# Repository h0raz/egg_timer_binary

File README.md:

egg_timer_binary
===================

This is/will be a egg timer with a battery powered binary display

It shows either the minutes in 6 bits and the seconds or if time is greater than one hour the hour and the minutes and the seconds ticking

If the timer reaches zero it will beep until the rotary encoder is pressed

While the timer is not active you can change the timer by turning the encoder. Start/Pause, Reset is a Push on the encoder

If the seconds are not zero(eg you paused it) and you change the time the seconds will be set to 0

I set the OSCCAL so the drift is minimal and I don't need any crystal

As you can asume this project is still in development

The firmware is functional and finished for now but the layout needs some tweaking and I'm currently searching for a case which has the right size

> **Todo/Bugs:**
> 
> - Power down mode after a timeout
> - generalize Pin/Port settings
> - translate comments etc.
> - sound is a bit aweful
> - PCB desing
> - find case

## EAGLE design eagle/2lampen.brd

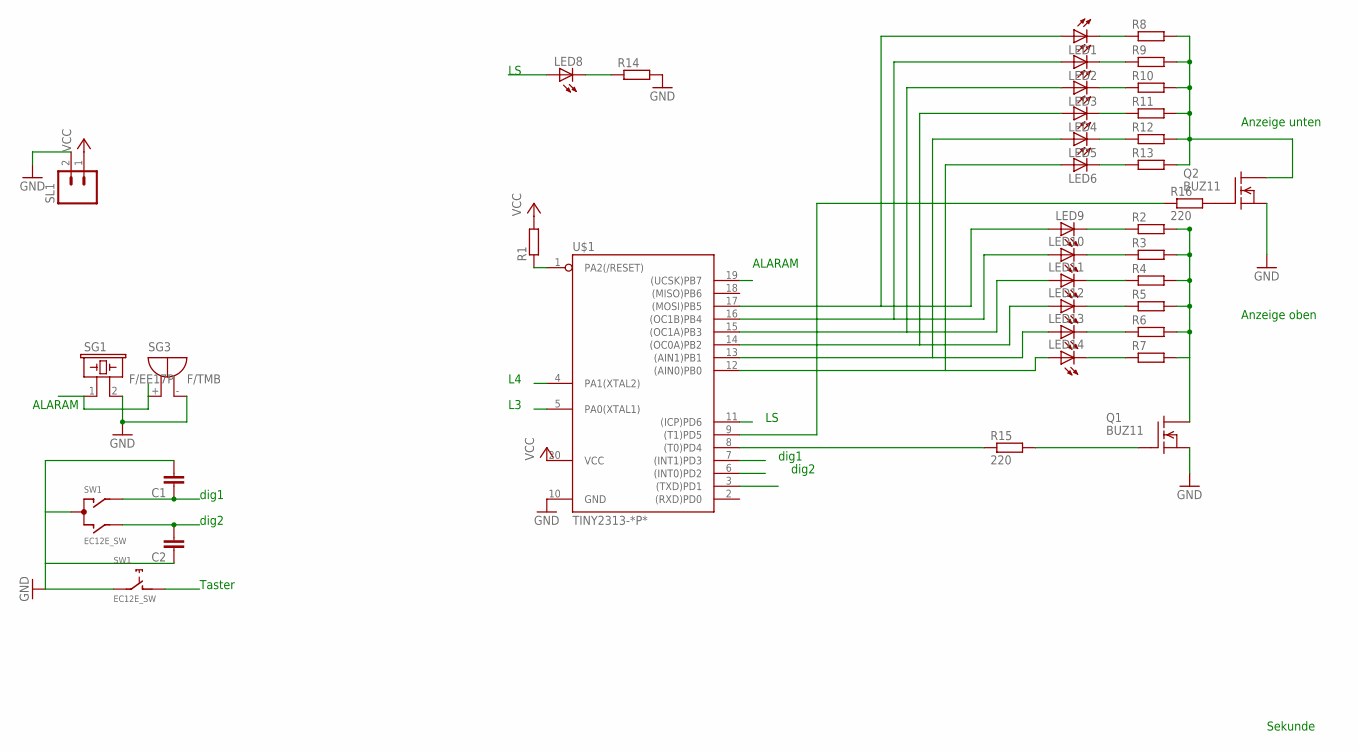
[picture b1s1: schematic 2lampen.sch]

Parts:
C1, C2: C-EU025-025X050; C025-025X050
LED1, LED2, LED3, LED4, LED5, LED6, LED9, LED10, LED11, LED12, LED13, LED14: LED5MM
LED8: LED3MM
Q1, Q2: BUZ11; TO220
R1, R13: R-EU_0204/7; 0204/7
R2, R3, R4, R5, R6, R7, R8, R9, R10, R11, R12, R14: R-EU_0204/2V; 0204V
R15, R16: 220; 0204V
SG1: F/EE17P
SG3: F/TMB
SL1: M02; 02P
SW1: EC12E_SW; ALPS_EC12E_SW
U$1: TINY2313-*P*; DIL20

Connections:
ALARM: SG1.1, SG3.+, U$1.19 ((UCSK)PB7)
DIG1: C1.1, SW1.A, U$1.7 ((INT1)PD3)
DIG2: C2.2, SW1.B, U$1.6 ((INT0)PD2)
GND: C1.2, C2.1, Q1.3 (S), Q2.3 (S), R14.2, SG1.2, SG3.-, SL1.2, SW1.C, SW1.E (2), U$1.10 (GND)
L1: LED1.A, LED9.A, U$1.17 ((MOSI)PB5)
L2: LED2.A, LED10.A, U$1.16 ((OC1B)PB4)
L3: LED3.A, LED11.A, U$1.5 (PA0(XTAL1)), U$1.15 ((OC1A)PB3)
L4: LED4.A, LED12.A, U$1.4 (PA1(XTAL2)), U$1.14 ((OC0A)PB2)
L5: LED5.A, LED13.A, U$1.13 ((AIN1)PB1)
L6: LED6.A, LED14.A, U$1.12 ((AIN0)PB0)
LS: LED8.A, U$1.11 ((ICP)PD6)
unnamed: LED6.K (C), R13.1
unnamed: LED5.K (C), R12.1
unnamed: LED4.K (C), R11.1
unnamed: LED3.K (C), R10.1
unnamed: Q1.2 (D), R2.2, R3.2, R4.2, R5.2, R6.2, R7.2
unnamed: LED2.K (C), R9.1
unnamed: LED1.K (C), R8.1
unnamed: LED8.K (C), R14.1
unnamed: LED9.K (C), R2.1
unnamed: LED10.K (C), R3.1
unnamed: LED11.K (C), R4.1
unnamed: LED12.K (C), R5.1
unnamed: LED13.K (C), R6.1
unnamed: LED14.K (C), R7.1
unnamed: Q2.2 (D), R8.2, R9.2, R10.2, R11.2, R12.2, R13.2
unnamed: Q1.1 (G), R15.2
unnamed: Q2.1 (G), R16.2
unnamed: R16.1, U$1.9 ((T1)PD5)
unnamed: R15.1, U$1.8 ((T0)PD4)
RESET: R1.1, U$1.1 (PA2(/RESET))
TAST: SW1.D (1)
VCC: R1.2, SL1.1, U$1.20 (VCC)

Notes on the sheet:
ALARAM
dig1
dig2
Taster
Anzeige oben
Anzeige unten
Sekunde

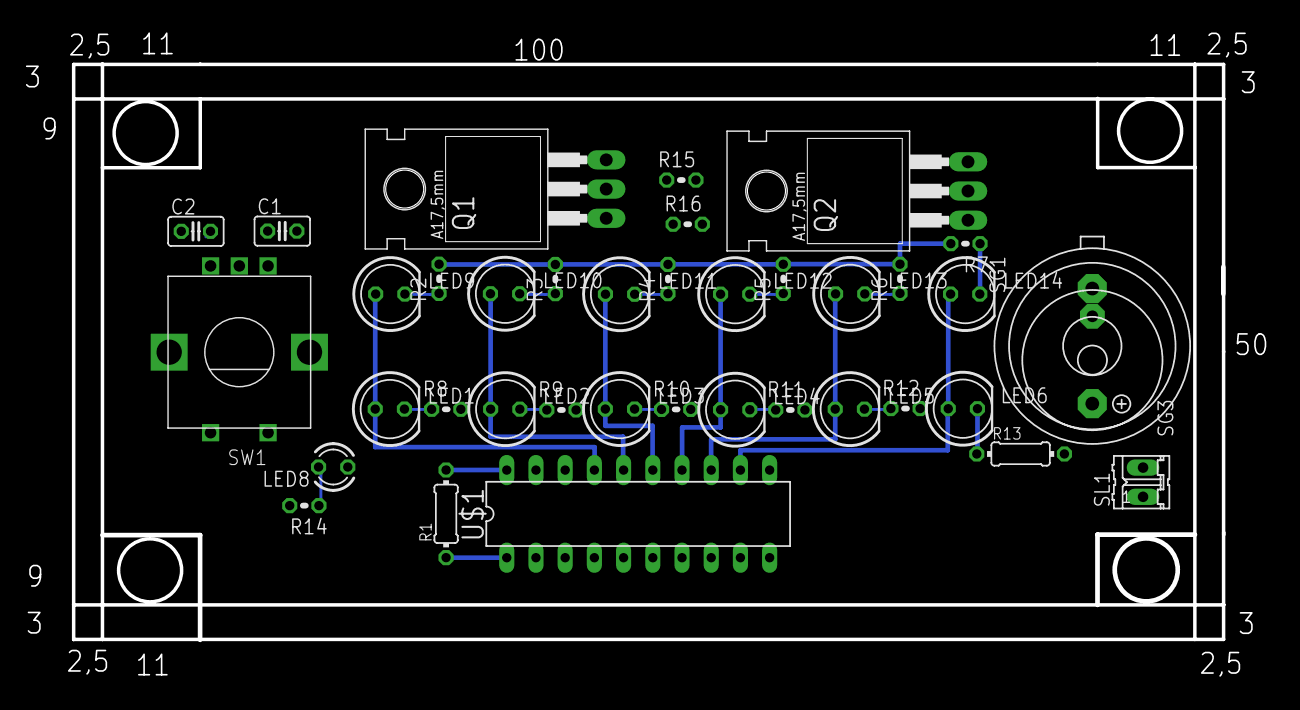
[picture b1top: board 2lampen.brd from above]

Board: 2 copper layers, 108.6 x 57.3 mm, 38 parts (0 on the bottom side), 32 nets.

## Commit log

2014-02-27 data init
